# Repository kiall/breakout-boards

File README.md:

Breakout Boards
===============

1. [RFM69-ESP-03](RFM69-ESP-03/README.md) - Combination breakout for the RFM69 RF module, and the ESP-03 wifi module.

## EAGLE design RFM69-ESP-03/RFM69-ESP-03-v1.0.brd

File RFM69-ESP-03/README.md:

RFM69 / ESP-03 Breakout Board
=============================

Combination breakout for the RFM69 RF module, and the ESP-03 wifi module.

Status
------

Currently unproven, order has been sent to fab.

Revision History
----------------

* v1.0 - Inital Board
* v1.x (WIP)
 * Add revision number to silkscreen

Notes
-----

* SJ1 can be closed for when using an RFM69, it will join both grounds on the RFM69 together.
* Pad AP can be used when using an RFM69, as a location for soldering a wire antenna. 

Board
-----

Front:

Back:

Panel Board
-----------

Front:

Back:

Schematic
---------

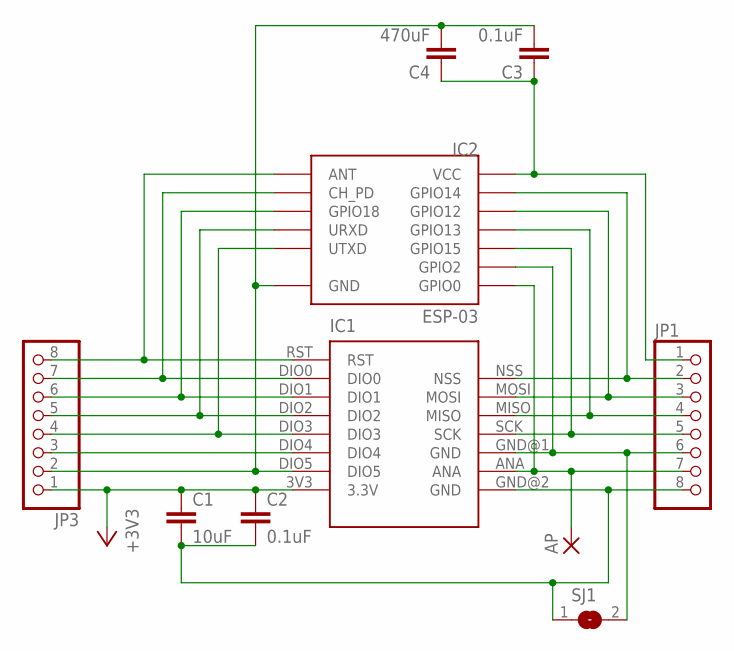
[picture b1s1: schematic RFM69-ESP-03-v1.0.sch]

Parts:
AP: SMD5; SMD2,54-5,08
C1: 10uF; C1206
C2, C3: 0.1uF; C1206
C4: 470uF; C1206
IC1: RFM69HW; RFM69
IC2: ESP-03
JP1, JP3: PINHD-1X8; 1X08
SJ1: SJ

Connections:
+3V3: C1.1, C2.1, IC1.3V3 (3.3V), JP3.1
unnamed: IC1.NSS, IC2.GPIO14, JP1.2
unnamed: IC1.MOSI, IC2.GPIO12, JP1.3
unnamed: IC1.MISO, IC2.GPIO13, JP1.4
unnamed: IC1.SCK, IC2.GPIO15, JP1.5
unnamed: AP.1, IC1.ANA, IC2.GPIO0, JP1.7
unnamed: C3.1, C4.1, IC2.VCC, JP1.1
unnamed: IC1.GND@1 (GND), IC2.GPIO2, JP1.6, SJ1.2
unnamed: IC1.RST, IC2.ANT, JP3.8
unnamed: IC1.DIO0, IC2.CH_PD, JP3.7
unnamed: IC1.DIO1, IC2.GPIO18, JP3.6
unnamed: IC1.DIO2, IC2.URXD, JP3.5
unnamed: IC1.DIO3, IC2.UTXD, JP3.4
unnamed: IC1.DIO4, JP3.3
unnamed: C1.2, C2.2, IC1.GND@2 (GND), JP1.8, SJ1.1
unnamed: C3.2, C4.2, IC1.DIO5, IC2.GND, JP3.2

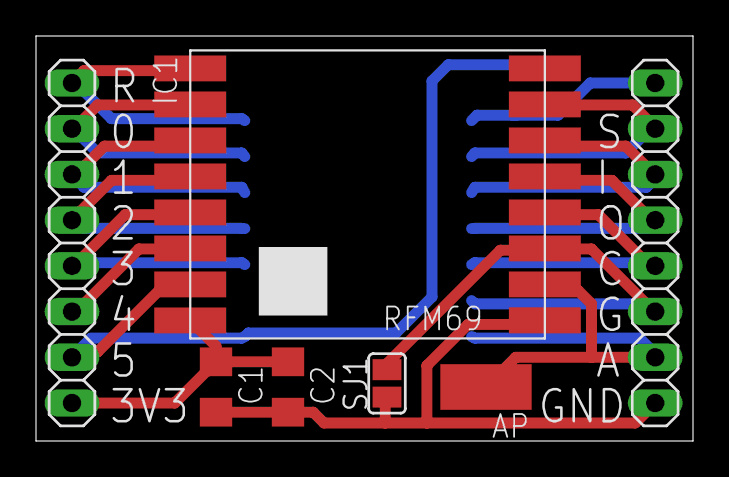
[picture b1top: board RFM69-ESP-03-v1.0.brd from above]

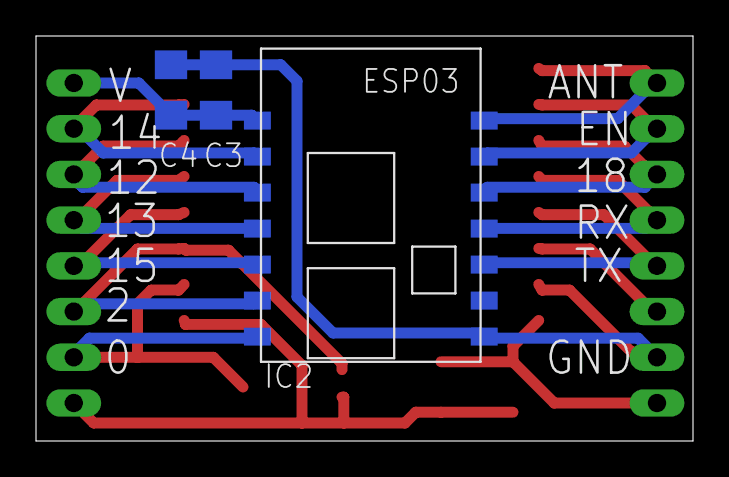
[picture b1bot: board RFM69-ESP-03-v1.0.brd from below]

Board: 2 copper layers, 36.5 x 22.5 mm, 10 parts (3 on the bottom side), 16 nets.

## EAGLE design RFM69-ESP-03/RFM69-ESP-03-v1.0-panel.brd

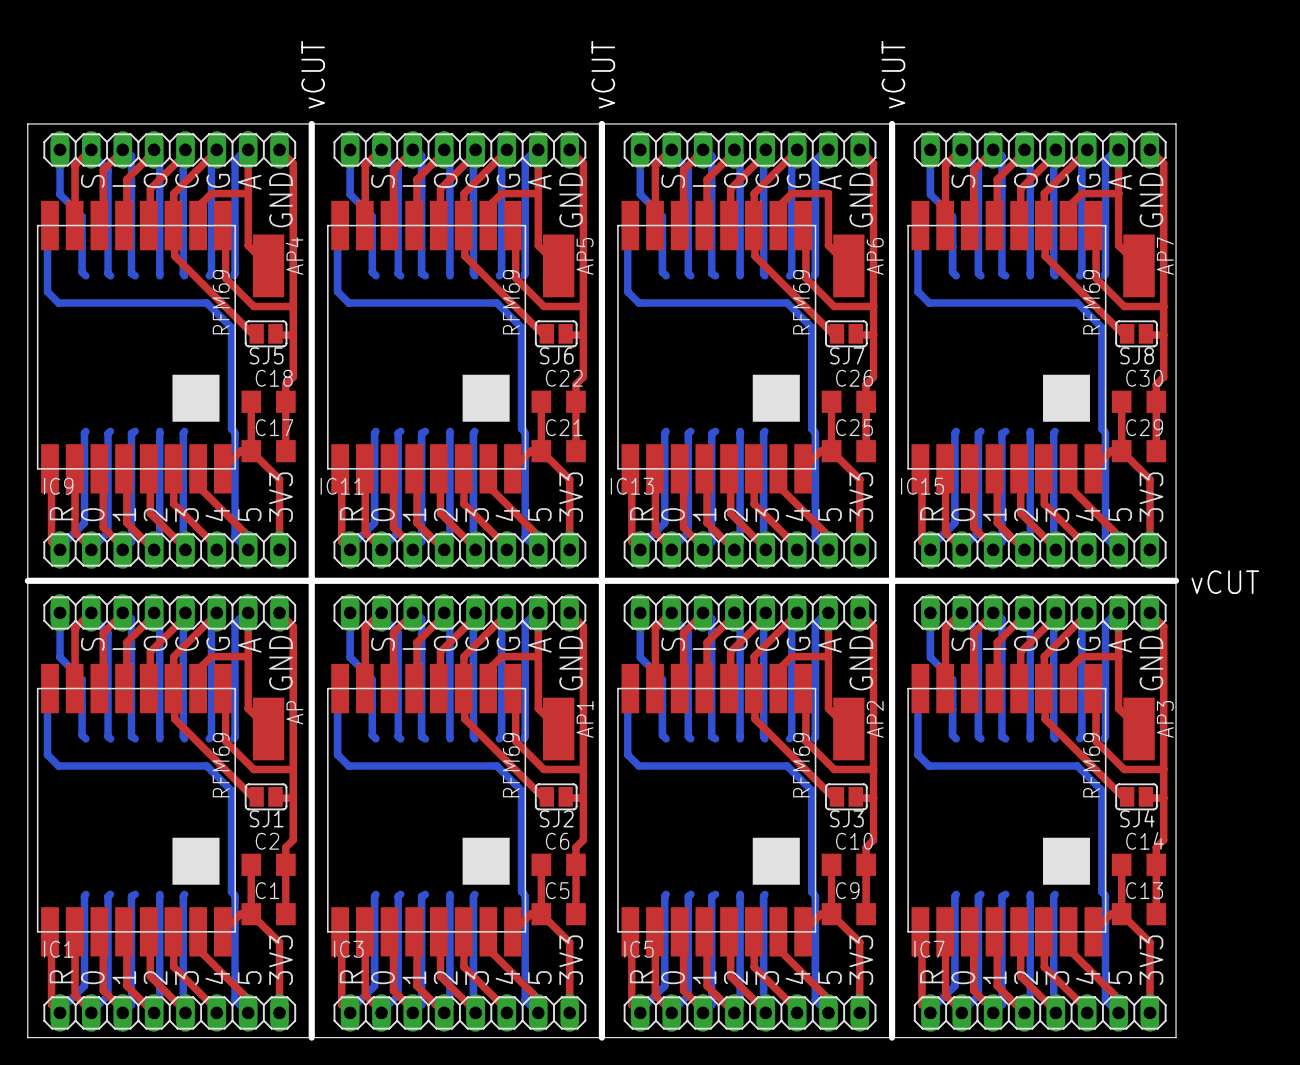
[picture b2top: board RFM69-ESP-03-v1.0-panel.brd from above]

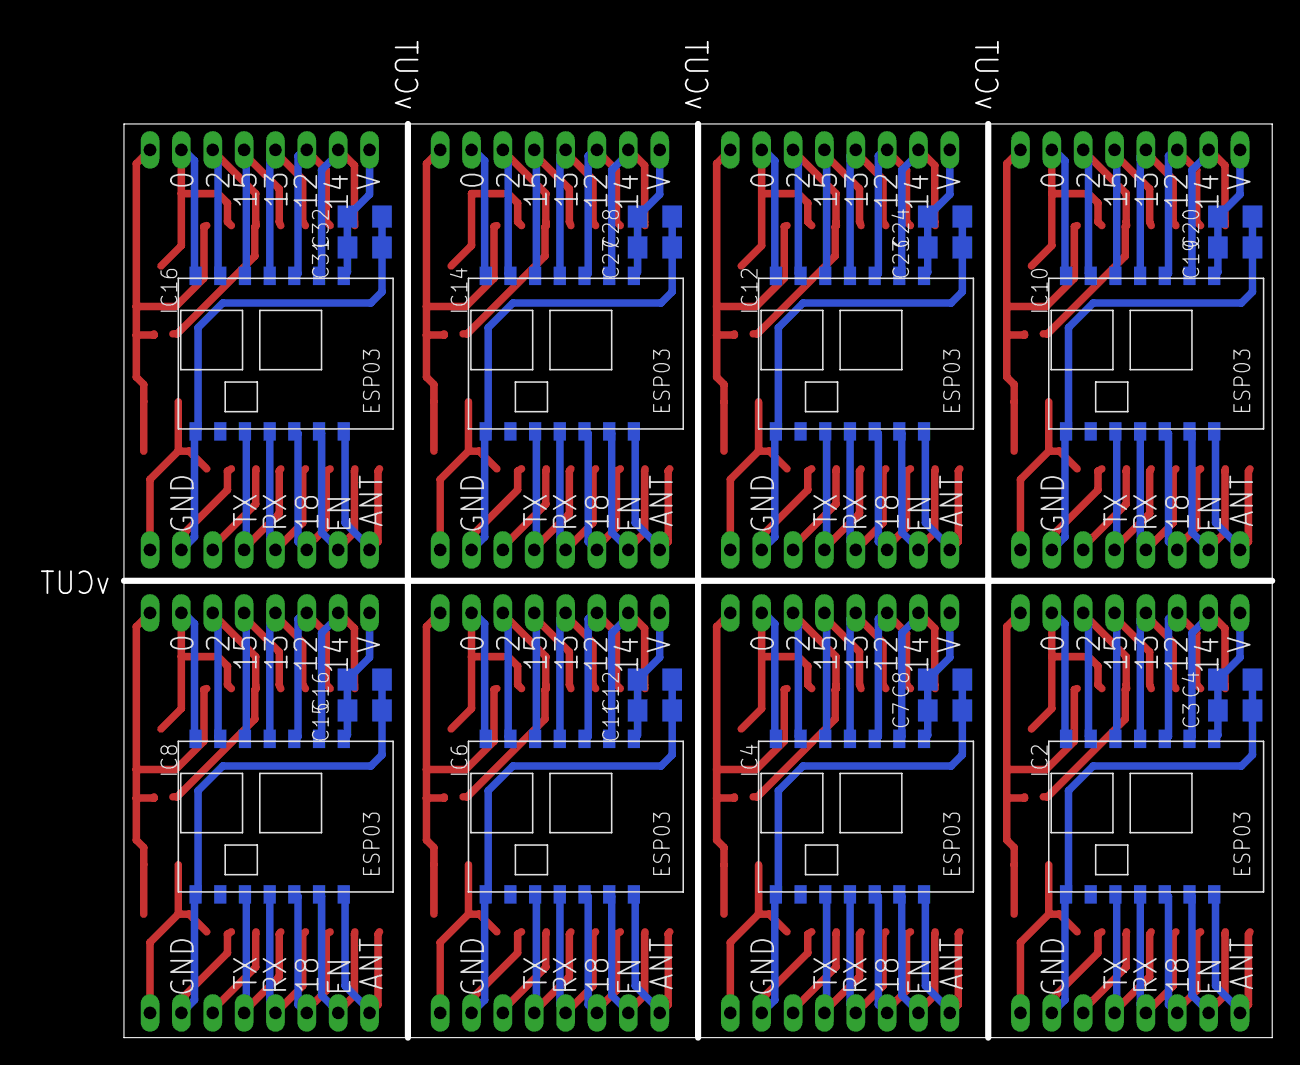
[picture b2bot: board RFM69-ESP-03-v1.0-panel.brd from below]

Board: 2 copper layers, 100.8 x 81.8 mm, 80 parts (24 on the bottom side), 129 nets.

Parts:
AP, AP1, AP2, AP3, AP4, AP5, AP6, AP7: SMD2,54-5,08
C1, C5, C9, C13, C17, C21, C25, C29: 10uF; C1206
C2, C3, C6, C7, C10, C11, C14, C15, C18, C19, C22, C23, C26, C27, C30, C31: 0.1uF; C1206
C4, C8, C12, C16, C20, C24, C28, C32: 470uF; C1206
IC1, IC3, IC5, IC7, IC9, IC11, IC13, IC15: RFM69HW; RFM69
IC2, IC4, IC6, IC8, IC10, IC12, IC14, IC16: ESP-03
JP1, JP2, JP3, JP4, JP5, JP6, JP7, JP8, JP9, JP10, JP11, JP12, JP13, JP14, JP15, JP16: 1X08
SJ1, SJ2, SJ3, SJ4, SJ5, SJ6, SJ7, SJ8: SJ

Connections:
+3V1: C5.1, C6.1, IC3.3V3, JP4.1
+3V2: C9.1, C10.1, IC5.3V3, JP6.1
+3V3: C1.1, C2.1, IC1.3V3, JP3.1
+3V4: C13.1, C14.1, IC7.3V3, JP8.1
+3V5: C17.1, C18.1, IC9.3V3, JP10.1
+3V6: C21.1, C22.1, IC11.3V3, JP12.1
+3V7: C25.1, C26.1, IC13.3V3, JP14.1
+3V8: C29.1, C30.1, IC15.3V3, JP16.1
unnamed: IC1.NSS, IC2.GPIO14, JP1.2
unnamed: IC1.MOSI, IC2.GPIO12, JP1.3
unnamed: IC1.MISO, IC2.GPIO13, JP1.4
unnamed: IC1.SCK, IC2.GPIO15, JP1.5
unnamed: AP.1, IC1.ANA, IC2.GPIO0, JP1.7
unnamed: C3.1, C4.1, IC2.VCC, JP1.1
unnamed: IC1.GND@1, IC2.GPIO2, JP1.6, SJ1.2
unnamed: IC1.RST, IC2.ANT, JP3.8
unnamed: IC1.DIO0, IC2.CH_PD, JP3.7
unnamed: IC1.DIO1, IC2.GPIO18, JP3.6
unnamed: IC1.DIO2, IC2.URXD, JP3.5
unnamed: IC1.DIO3, IC2.UTXD, JP3.4
unnamed: IC1.DIO4, JP3.3
unnamed: IC15.NSS, IC16.GPIO14, JP15.2
unnamed: C1.2, C2.2, IC1.GND@2, JP1.8, SJ1.1
unnamed: C3.2, C4.2, IC1.DIO5, IC2.GND, JP3.2
unnamed: IC15.MOSI, IC16.GPIO12, JP15.3
unnamed: IC15.MISO, IC16.GPIO13, JP15.4
unnamed: IC15.SCK, IC16.GPIO15, JP15.5
unnamed: IC3.NSS, IC4.GPIO14, JP2.2
unnamed: IC3.MOSI, IC4.GPIO12, JP2.3
unnamed: IC15.RST, IC16.ANT, JP16.8
unnamed: IC15.DIO0, IC16.CH_PD, JP16.7
unnamed: IC15.DIO1, IC16.GPIO18, JP16.6
unnamed: IC3.MISO, IC4.GPIO13, JP2.4
unnamed: IC3.SCK, IC4.GPIO15, JP2.5
unnamed: IC3.RST, IC4.ANT, JP4.8
unnamed: IC3.DIO0, IC4.CH_PD, JP4.7
unnamed: IC3.DIO1, IC4.GPIO18, JP4.6
unnamed: IC3.DIO2, IC4.URXD, JP4.5
unnamed: IC5.NSS, IC6.GPIO14, JP5.2
unnamed: IC5.MOSI, IC6.GPIO12, JP5.3
unnamed: IC5.MISO, IC6.GPIO13, JP5.4
unnamed: IC5.SCK, IC6.GPIO15, JP5.5
unnamed: IC5.RST, IC6.ANT, JP6.8
unnamed: IC5.DIO0, IC6.CH_PD, JP6.7
unnamed: IC5.DIO1, IC6.GPIO18, JP6.6
unnamed: IC5.DIO2, IC6.URXD, JP6.5
unnamed: IC5.DIO3, IC6.UTXD, JP6.4
unnamed: IC5.DIO4, JP6.3
unnamed: AP2.1, IC5.ANA, IC6.GPIO0, JP5.7
unnamed: C11.1, C12.1, IC6.VCC, JP5.1
unnamed: C9.2, C10.2, IC5.GND@2, JP5.8, SJ3.1
unnamed: IC5.GND@1, IC6.GPIO2, JP5.6, SJ3.2
unnamed: C11.2, C12.2, IC5.DIO5, IC6.GND, JP6.2
unnamed: IC7.NSS, IC8.GPIO14, JP7.2
unnamed: IC7.MOSI, IC8.GPIO12, JP7.3
unnamed: IC7.MISO, IC8.GPIO13, JP7.4
unnamed: IC7.SCK, IC8.GPIO15, JP7.5
unnamed: IC7.RST, IC8.ANT, JP8.8
unnamed: IC7.DIO0, IC8.CH_PD, JP8.7
unnamed: IC7.DIO1, IC8.GPIO18, JP8.6
unnamed: IC7.DIO2, IC8.URXD, JP8.5
unnamed: IC7.DIO3, IC8.UTXD, JP8.4
unnamed: IC7.DIO4, JP8.3
unnamed: AP3.1, IC7.ANA, IC8.GPIO0, JP7.7
unnamed: C15.1, C16.1, IC8.VCC, JP7.1
unnamed: C13.2, C14.2, IC7.GND@2, JP7.8, SJ4.1
unnamed: IC7.GND@1, IC8.GPIO2, JP7.6, SJ4.2
unnamed: C15.2, C16.2, IC7.DIO5, IC8.GND, JP8.2
unnamed: IC9.NSS, IC10.GPIO14, JP9.2
unnamed: IC9.MOSI, IC10.GPIO12, JP9.3
unnamed: IC9.MISO, IC10.GPIO13, JP9.4
unnamed: IC9.SCK, IC10.GPIO15, JP9.5
unnamed: IC9.RST, IC10.ANT, JP10.8
unnamed: IC9.DIO0, IC10.CH_PD, JP10.7
unnamed: IC9.DIO1, IC10.GPIO18, JP10.6
unnamed: IC9.DIO2, IC10.URXD, JP10.5
unnamed: IC9.DIO3, IC10.UTXD, JP10.4
unnamed: IC9.DIO4, JP10.3
unnamed: AP4.1, IC9.ANA, IC10.GPIO0, JP9.7
unnamed: C19.1, C20.1, IC10.VCC, JP9.1
unnamed: C17.2, C18.2, IC9.GND@2, JP9.8, SJ5.1
unnamed: IC9.GND@1, IC10.GPIO2, JP9.6, SJ5.2
unnamed: C19.2, C20.2, IC9.DIO5, IC10.GND, JP10.2
unnamed: IC11.NSS, IC12.GPIO14, JP11.2
unnamed: IC11.MOSI, IC12.GPIO12, JP11.3
unnamed: IC11.MISO, IC12.GPIO13, JP11.4
unnamed: IC11.SCK, IC12.GPIO15, JP11.5
unnamed: IC11.RST, IC12.ANT, JP12.8
unnamed: IC11.DIO0, IC12.CH_PD, JP12.7
unnamed: IC11.DIO1, IC12.GPIO18, JP12.6
unnamed: IC11.DIO2, IC12.URXD, JP12.5
unnamed: IC11.DIO3, IC12.UTXD, JP12.4
unnamed: IC11.DIO4, JP12.3
unnamed: AP5.1, IC11.ANA, IC12.GPIO0, JP11.7
unnamed: C23.1, C24.1, IC12.VCC, JP11.1
unnamed: C21.2, C22.2, IC11.GND@2, JP11.8, SJ6.1
unnamed: IC11.GND@1, IC12.GPIO2, JP11.6, SJ6.2
unnamed: C23.2, C24.2, IC11.DIO5, IC12.GND, JP12.2
unnamed: IC13.NSS, IC14.GPIO14, JP13.2
unnamed: IC13.MOSI, IC14.GPIO12, JP13.3
unnamed: IC13.MISO, IC14.GPIO13, JP13.4
unnamed: IC13.SCK, IC14.GPIO15, JP13.5
unnamed: IC13.RST, IC14.ANT, JP14.8
unnamed: IC13.DIO0, IC14.CH_PD, JP14.7
unnamed: IC13.DIO1, IC14.GPIO18, JP14.6
unnamed: IC13.DIO2, IC14.URXD, JP14.5
unnamed: IC13.DIO3, IC14.UTXD, JP14.4
unnamed: IC13.DIO4, JP14.3
unnamed: IC14.GPIO0, JP13.7
unnamed: C27.1, C28.1, IC14.VCC, JP13.1
unnamed: C25.2, C26.2, IC13.GND@2, JP13.8, SJ7.1
unnamed: IC13.GND@1, IC14.GPIO2, JP13.6, SJ7.2
unnamed: C27.2, C28.2, IC13.DIO5, IC14.GND, JP14.2
unnamed: IC15.DIO2, IC16.URXD, JP16.5
unnamed: IC15.DIO3, IC16.UTXD, JP16.4
unnamed: IC15.DIO4, JP16.3
unnamed: AP7.1, IC15.ANA, IC16.GPIO0, JP15.7
unnamed: C31.1, C32.1, IC16.VCC, JP15.1
unnamed: C29.2, C30.2, IC15.GND@2, JP15.8, SJ8.1
unnamed: IC15.GND@1, IC16.GPIO2, JP15.6, SJ8.2
unnamed: C31.2, C32.2, IC15.DIO5, IC16.GND, JP16.2
unnamed: IC3.DIO3, IC4.UTXD, JP4.4
unnamed: IC3.DIO4, JP4.3
unnamed: AP1.1, IC3.ANA, IC4.GPIO0, JP2.7
unnamed: C7.1, C8.1, IC4.VCC, JP2.1
unnamed: C5.2, C6.2, IC3.GND@2, JP2.8, SJ2.1
unnamed: IC3.GND@1, IC4.GPIO2, JP2.6, SJ2.2
unnamed: C7.2, C8.2, IC3.DIO5, IC4.GND, JP4.2
S$2: AP6.1, IC13.ANA

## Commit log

2016-12-21 Add RFM69 / ESP-03 Breakout Board
2016-12-21 RFM69-ESP-03 v1.0 Board RfM
2016-12-21 Add README's and pictures
2016-12-21 Add a name+revision mumber to RFM69-ESP-03 board
2016-12-23 Add note on board status
2016-12-23 Add Revision History
